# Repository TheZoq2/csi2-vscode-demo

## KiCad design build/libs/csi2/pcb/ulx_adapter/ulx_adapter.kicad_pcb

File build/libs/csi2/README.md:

# Spade CSI2

Work in progress Spade library for parsing CSI2 data streams like those coming
out of the raspberry pi camera.

Currently being tested on a ULX3s with a hacked together camera connector ->
PMOD differential pair adapter. The initial i2c setup of the camera is done by
the `i2c_driver` running on an stm32f103 microcontroller whose i2c pins are
connected to the camera's.

Big thanks to gatecat for their CSI2 verilog implementation here https://github.com/gatecat/CSI2Rx.

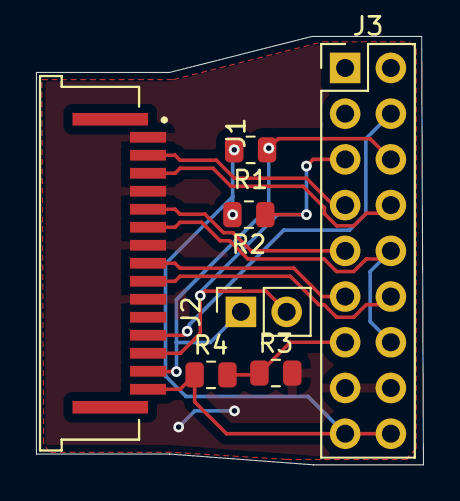
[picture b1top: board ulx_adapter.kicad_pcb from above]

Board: 2 copper layers, 21.5 x 23.8 mm, 7 parts (0 on the bottom side), 12 nets.

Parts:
J1: Conn_01x15_Pin; AMPHENOL_SFW15R-2STE1LF
J2: Conn_01x02_Pin; PinSocket_1x02_P2.54mm_Vertical
J3: Conn_02x09_Odd_Even; PinHeader_2x09_P2.54mm_Vertical
R1, R2, R4: 10k; R_0805_2012Metric
R3: 30k; R_0805_2012Metric

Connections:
+3V3: J1.15, J3.17, J3.18, R1.2, R2.2, R4.1
CLKN: J1.8, J3.11
CLKP: J1.9, J3.12
D0_N: J1.2, J3.7
D0_P: J1.3, J3.8
D1_N: J1.5, J3.9
D1_P: J1.6, J3.10, J3.14
GN14: J3.13, R3.1, R4.2
GN18: J1.13, J2.2, J3.5, R2.1
GND: J1.1, J1.4, J1.7, J1.10, J3.15, J3.16, R3.2
GP18: J1.14, J2.1, J3.6, R1.1
GP19: J1.12, J3.4

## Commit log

2024-06-02 Add VScode stuff
2024-06-02 Remove build and use main branch for everything
